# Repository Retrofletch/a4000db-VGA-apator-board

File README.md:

# a4000db-VGA-apator-board
small pcb that allows you to connect a VGA connector and bracket to arananets A4000db board

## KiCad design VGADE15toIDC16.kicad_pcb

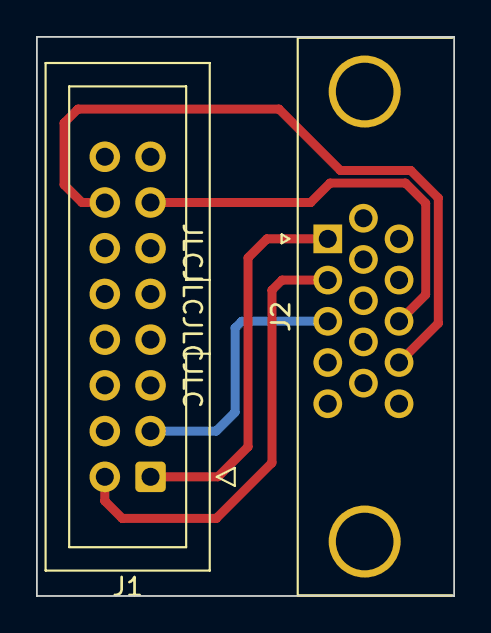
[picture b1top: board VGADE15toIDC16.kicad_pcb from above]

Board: 2 copper layers, 23.2 x 31.1 mm, 3 parts (1 on the bottom side), 7 nets.

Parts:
 : LOGO; 8mm fletch
J1: IDC-Header_2x08_P2.54mm_Vertical
J2: DSUB-15-HD_Female_Horizontal_P2.29x1.98mm_EdgePinOffset3.03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

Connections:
/BLUE: J1.3, J2.3
/GND: J1.6, J1.7, J1.8, J1.10, J2.0, J2.5, J2.6, J2.7, J2.8, J2.10
/GREEN: J1.2, J2.2
/HSYNC: J1.13, J2.13
/NC: J1.4, J1.5, J1.9, J1.11, J1.12, J1.15, J2.4, J2.9, J2.11, J2.12, J2.15
/RED: J1.1, J2.1
/VSYNC: J1.14, J2.14
